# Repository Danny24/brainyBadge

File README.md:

# Brainy - The PCB badge
I had a brain surgery 2 weeks ago, I got a VP shunt due to a tumor in my tectal plate that was causing hydrocephalus. The tumor can't be removed, it's to risky. But with the valve I am going to be ok for a while. Some people helped me, so I made this badge for them. 

You could also help me with medical expenses purchasing this badge!
https://www.tindie.com/products/danny024/brainy-the-brain-badge/

And also you can read the full story!
https://hackaday.io/project/170993-brainy-the-pcb-badge

I created this PCB badge after having a brain surgery to remember it and celebrate that everything went fine!

Thank you!

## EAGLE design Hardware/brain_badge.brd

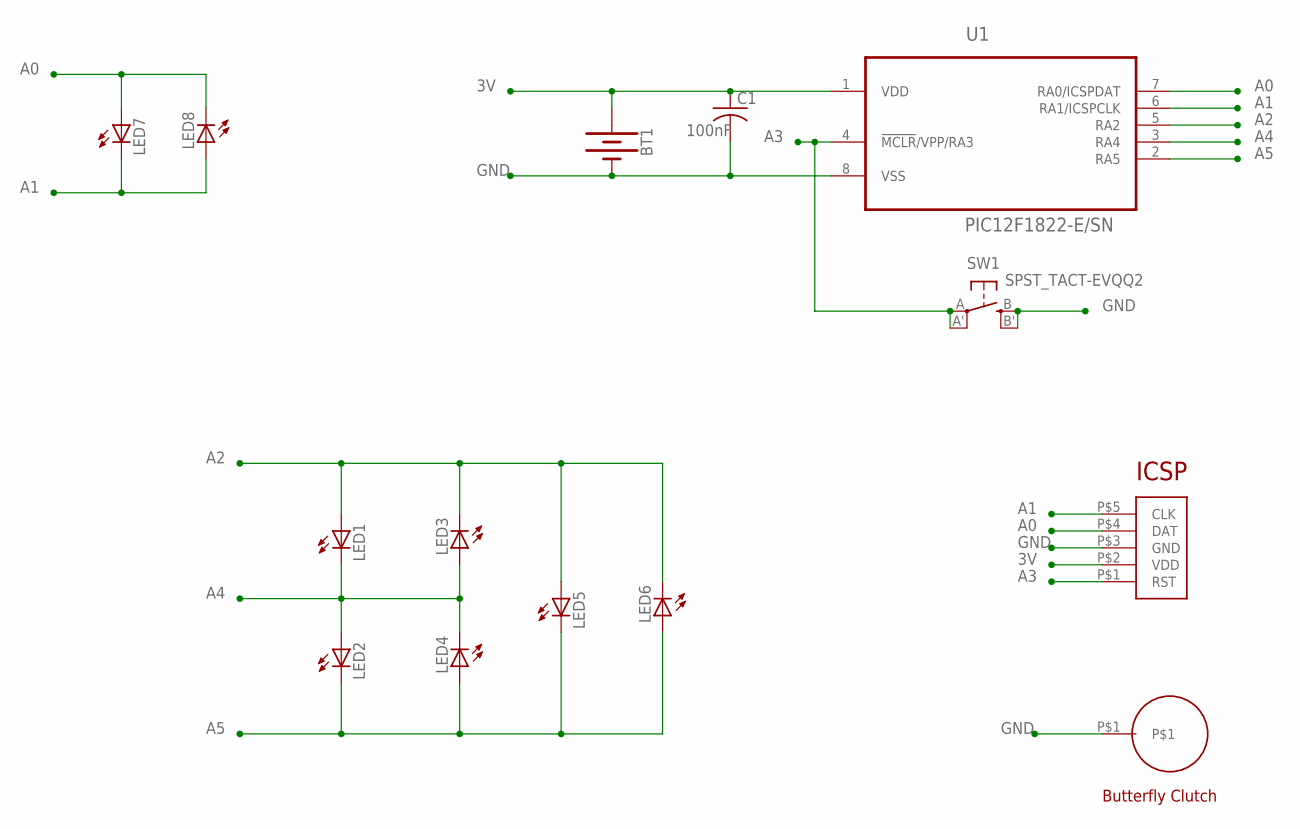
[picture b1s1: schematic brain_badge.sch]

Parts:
BT1: BATTERY-20MM_SMD; BATTCON_20MM
C1: 100nF; C0603K
LED1, LED2, LED3, LED4, LED5, LED6, LED7, LED8: LEDCHIP-LED0603; CHIP-LED0603
SW1: SPST_TACT-EVQQ2; EVQ-Q2
U1: PIC12F1822-E/SN; SOIC127P600X175-8N
U$1: ICSP_POGO
U$2: BUTTERFLY_CLUTCH

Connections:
3V: BT1.1 (+), BT1.3 (+), C1.1, U1.1 (VDD), U$1.P$2 (VDD)
A0: LED7.A, LED8.C, U1.7 (RA0/ICSPDAT), U$1.P$4 (DAT)
A1: LED7.C, LED8.A, U1.6 (RA1/ICSPCLK), U$1.P$5 (CLK)
A2: LED1.A, LED3.C, LED5.A, LED6.C, U1.5 (RA2)
A3: SW1.A, SW1.A' (P1), U1.4 (!MCLR!/VPP/RA3), U$1.P$1 (RST)
A4: LED1.C, LED2.A, LED3.A, LED4.C, U1.3 (RA4)
A5: LED2.C, LED4.A, LED5.C, LED6.A, U1.2 (RA5)
GND: BT1.2 (-), C1.2, SW1.B (S), SW1.B' (S1), U1.8 (VSS), U$1.P$3 (GND), U$2.P$1

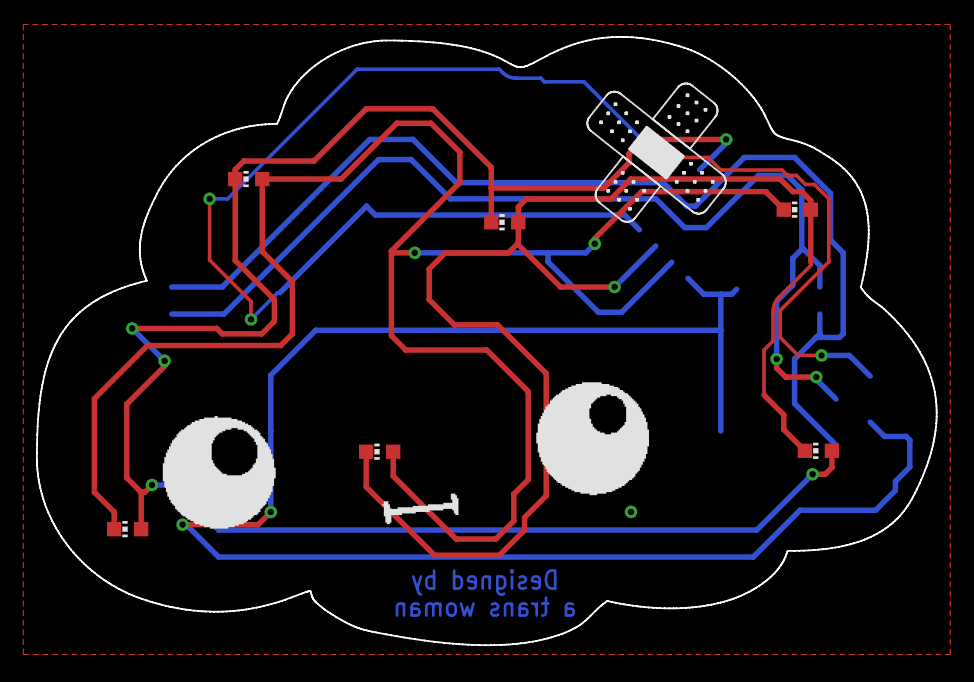
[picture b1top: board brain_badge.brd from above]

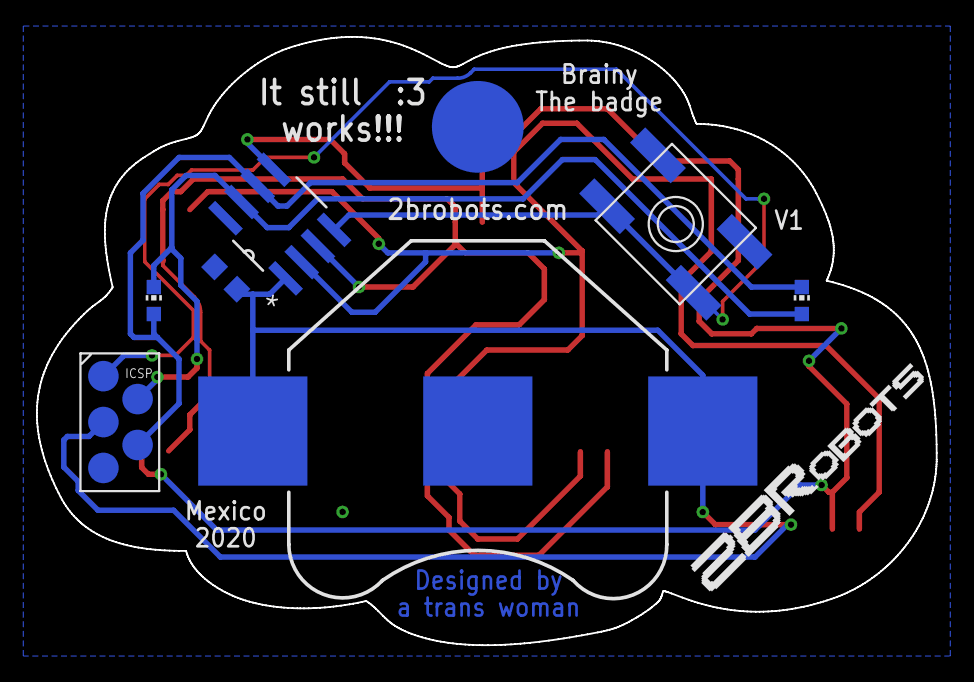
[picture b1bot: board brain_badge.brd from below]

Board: 2 copper layers, 50.0 x 33.8 mm, 14 parts (8 on the bottom side), 8 nets.

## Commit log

2020-04-15 Release badge
2020-04-15 release

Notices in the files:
parts and their libraries:
SparkFun-Batteries: Licensing: Creative Commons ShareAlike 4.0 International - https://creativecommons.org/licenses/by-sa/4.0
